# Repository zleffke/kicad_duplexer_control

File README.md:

# kicad_duplexer_control
Control Board for VTGS SX-Band System Duplexer Subsystem.  Controls failsafe 28V transfer switch position and 12V LNA.

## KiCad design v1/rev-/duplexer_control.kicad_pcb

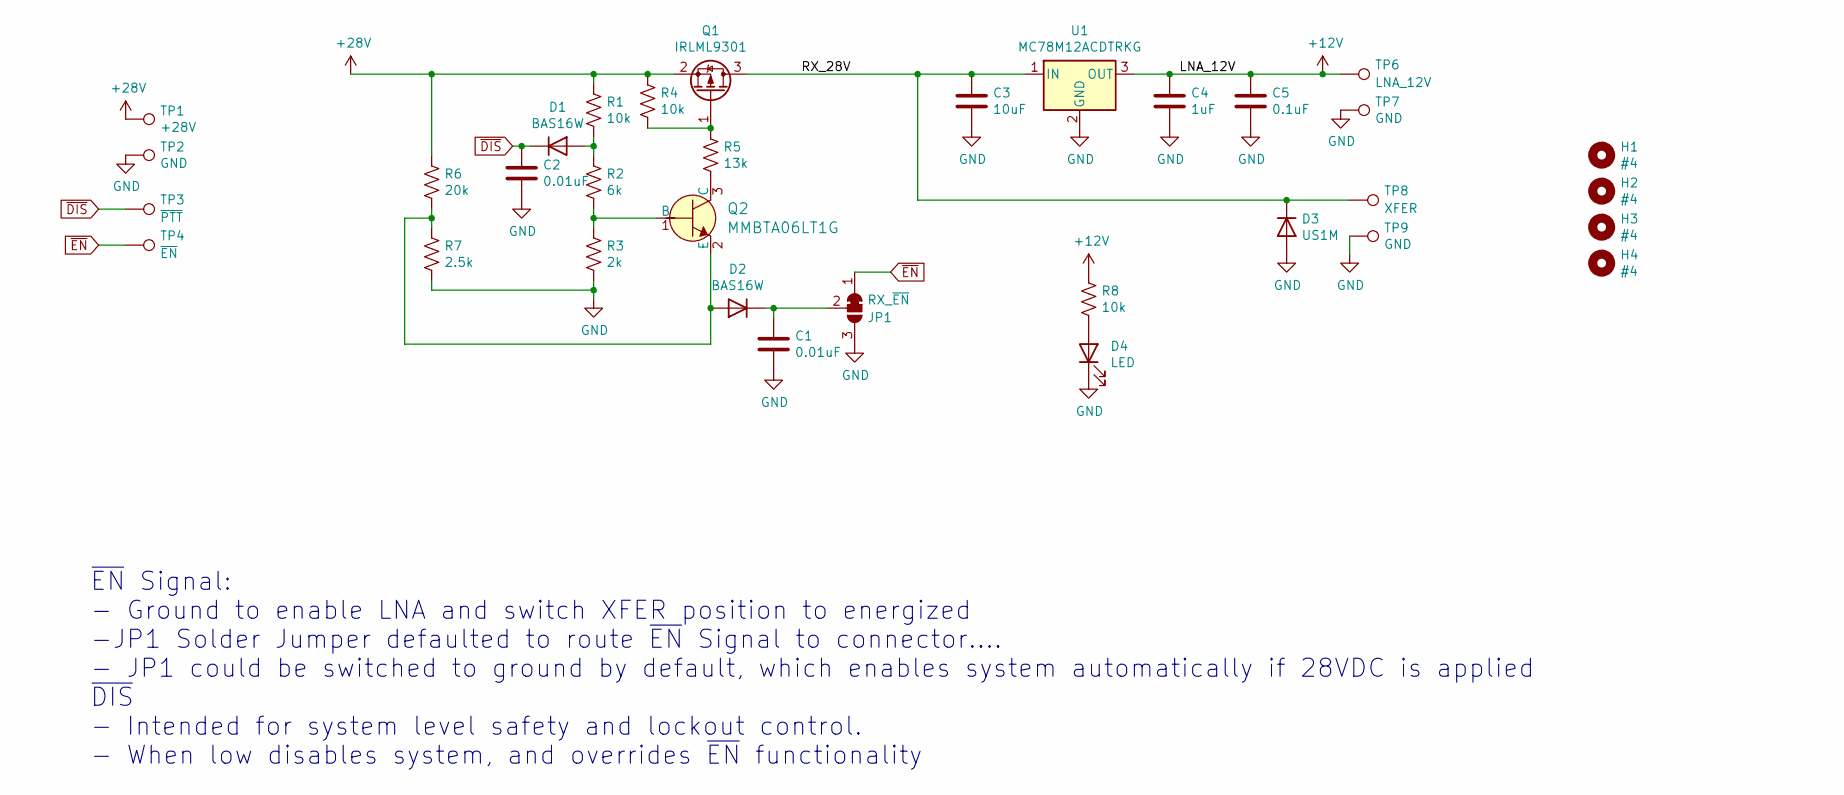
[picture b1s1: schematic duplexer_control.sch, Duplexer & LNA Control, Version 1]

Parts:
C1, C2: 0.01uF; 0805
C3: 10uF; 0805
C4: 1uF; 0805
C5: 0.1uF; 0805
D1, D2: BAS16W; SOT-23-3
D3: US1M; D_SMA
D4: LED; LED_0805_2012Metric
H1, H2, H3, H4: #4; MountingHole_3.2mm_M3
JP1: RX_~EN; SolderJumper-3_P1.3mm_Bridged12_RoundedPad1.0x1.5mm_NumberL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
Q1: IRLML9301; SOT-23-3
Q2: MMBTA06LT1G; SOT-23-3; MPN MMBTA06LT1G; Digi-Key_PN MMBTA06LT1GOSCT-ND
R1, R4, R8: 10k; 0805
R2: 6k; 0805
R3: 2k; 0805
R5: 13k; 0805
R6: 20k; 0805
R7: 2.5k; 0805
TP1: +28V; TestPoint_Pad_2.5x2.5mm
TP2, TP7, TP9: GND; TestPoint_Pad_2.5x2.5mm
TP3: ~PTT; TestPoint_Pad_2.5x2.5mm
TP4: ~EN; TestPoint_Pad_2.5x2.5mm
TP6: LNA_12V; TestPoint_Pad_2.5x2.5mm
TP8: XFER; TestPoint_Pad_2.5x2.5mm
U1: MC78M12ACDTRKG; TO-252-2

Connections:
+12V: C4.1, C5.1, R8.1, TP6.1, U1.3 (OUT)
+28V: Q1.2 (S), R1.1, R4.1, R6.1, TP1.1
/RX_28V: C3.1, D3.1 (K), Q1.3 (D), TP8.1, U1.1 (IN)
GND: C1.2, C2.2, C3.2, C4.2, C5.2, D3.2 (A), D4.1 (K), JP1.3 (B), R3.2, R7.2, TP2.1, TP7.1, TP9.1, U1.2 (GND)
unnamed: C1.1, D2.3 (K), JP1.2 (C)
unnamed: D1.1 (A), R1.2, R2.1
unnamed: D2.1 (A), Q2.2 (E), R6.2, R7.1
unnamed: D4.2 (A), R8.2
unnamed: Q1.1 (G), R4.2, R5.1
unnamed: Q2.1 (B), R2.2, R3.1
unnamed: Q2.3 (C), R5.2
~DIS: C2.1, D1.3 (K), TP3.1
~EN: JP1.1 (A), TP4.1

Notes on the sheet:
~EN~ Signal: - Ground to enable LNA and switch XFER position to energized -JP1 Solder Jumper defaulted to route ~EN~ Signal to connector.... - JP1 could be switched to ground by default, which enables system automatically if 28VDC is applied ~DIS~ - Intended for system level safety and lockout cont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

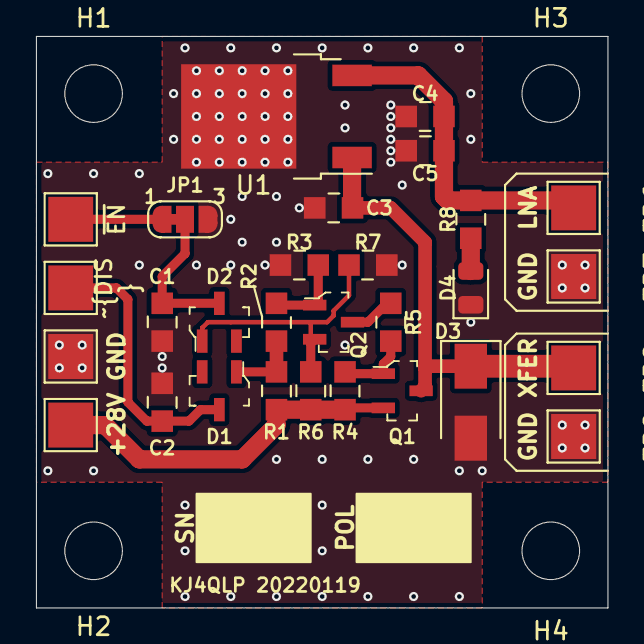
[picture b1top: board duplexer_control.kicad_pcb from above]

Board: 2 copper layers, 31.8 x 31.8 mm, 33 parts (0 on the bottom side), 13 nets.

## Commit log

2022-01-19 initial commit of completed V1, Rev-. This commit submitted to osh park 20220119

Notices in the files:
v1/rev-/duplexer_control.kicad_pcb:
License: CC BY 4.0
v1/rev-/duplexer_control.sch:
creativecommons.org/licenses/by/4.0
